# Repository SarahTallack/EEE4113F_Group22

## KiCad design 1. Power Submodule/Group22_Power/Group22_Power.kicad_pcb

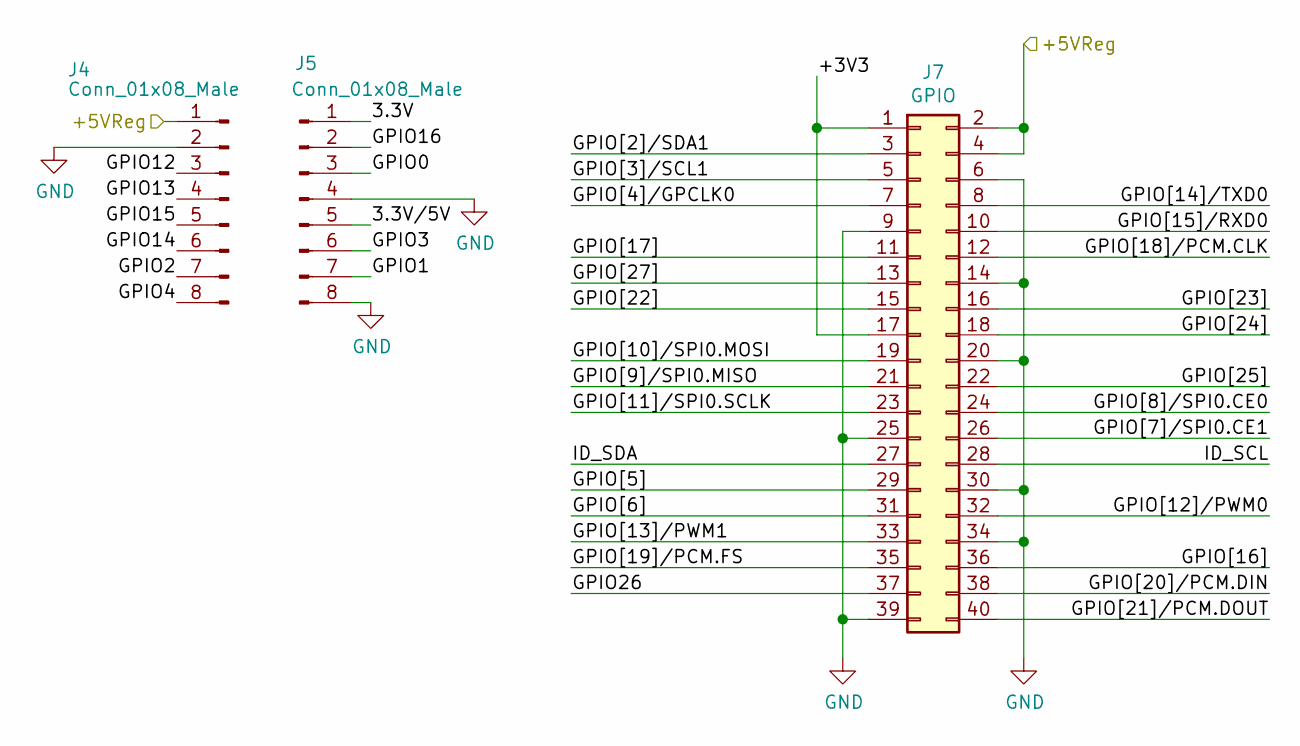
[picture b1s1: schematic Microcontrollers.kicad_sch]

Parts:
J4, J5: Conn_01x08_Male; PinSocket_1x08_P2.54mm_Vertical
J7: GPIO; PinSocket_2x20_P2.54mm_Vertical

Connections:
/Microcontrollers/3.3V: J5.1
/Microcontrollers/3.3V/5V: J5.5
/Microcontrollers/+3V3: J7.1, J7.17
/Microcontrollers/+5VReg: J4.1, J7.2, J7.4; also elsewhere on the board
/Microcontrollers/GPIO0: J5.3
/Microcontrollers/GPIO1: J5.7
/Microcontrollers/GPIO2: J4.7
/Microcontrollers/GPIO3: J5.6
/Microcontrollers/GPIO4: J4.8
/Microcontrollers/GPIO12: J4.3
/Microcontrollers/GPIO13: J4.4
/Microcontrollers/GPIO14: J4.6
/Microcontrollers/GPIO15: J4.5
/Microcontrollers/GPIO16: J5.2
/Microcontrollers/GPIO26: J7.37
/Microcontrollers/GPIO[2]/SDA1: J7.3
/Microcontrollers/GPIO[3]/SCL1: J7.5
/Microcontrollers/GPIO[4]/GPCLK0: J7.7
/Microcontrollers/GPIO[5]: J7.29
/Microcontrollers/GPIO[6]: J7.31
/Microcontrollers/GPIO[7]/SPI0.CE1: J7.26
/Microcontrollers/GPIO[8]/SPI0.CE0: J7.24
/Microcontrollers/GPIO[9]/SPI0.MISO: J7.21
/Microcontrollers/GPIO[10]/SPI0.MOSI: J7.19
/Microcontrollers/GPIO[11]/SPI0.SCLK: J7.23
/Microcontrollers/GPIO[12]/PWM0: J7.32
/Microcontrollers/GPIO[13]/PWM1: J7.33
/Microcontrollers/GPIO[14]/TXD0: J7.8
/Microcontrollers/GPIO[15]/RXD0: J7.10
/Microcontrollers/GPIO[16]: J7.36
/Microcontrollers/GPIO[17]: J7.11
/Microcontrollers/GPIO[18]/PCM.CLK: J7.12
/Microcontrollers/GPIO[19]/PCM.FS: J7.35
/Microcontrollers/GPIO[20]/PCM.DIN: J7.38
/Microcontrollers/GPIO[21]/PCM.DOUT: J7.40
/Microcontrollers/GPIO[22]: J7.15
/Microcontrollers/GPIO[23]: J7.16
/Microcontrollers/GPIO[24]: J7.18
/Microcontrollers/GPIO[25]: J7.22
/Microcontrollers/GPIO[27]: J7.13
/Microcontrollers/ID_SCL: J7.28
/Microcontrollers/ID_SDA: J7.27
GND: J4.2, J5.4, J5.8, J7.6, J7.9, J7.14, J7.20, J7.25, J7.30, J7.34, J7.39; also elsewhere on the board

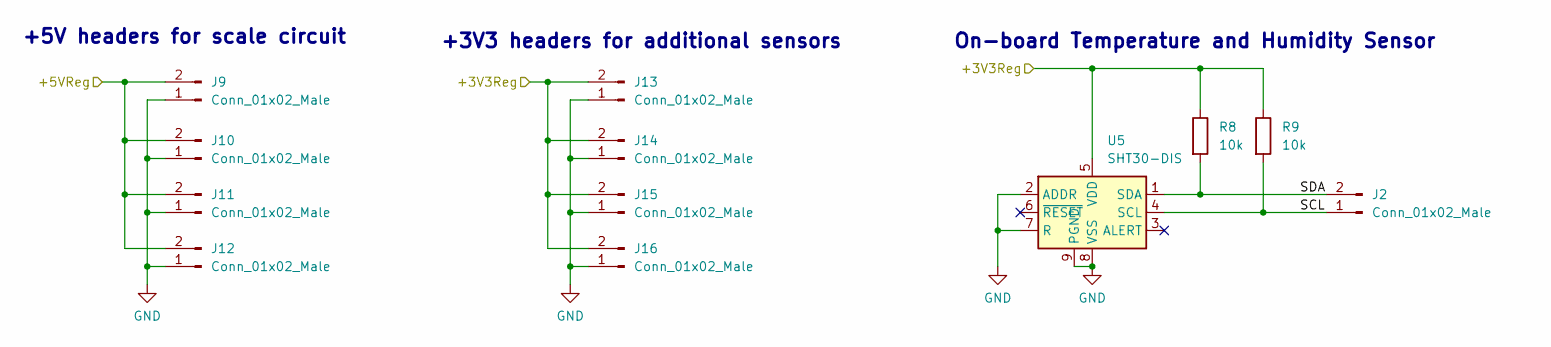
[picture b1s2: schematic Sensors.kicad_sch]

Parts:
J2, J9, J10, J11, J12, J13, J14, J15, J16: Conn_01x02_Male; PinHeader_1x02_P2.54mm_Vertical
R8, R9: 10k; R_0402_1005Metric; LCSC C25744
U5: SHT30-DIS; Sensirion_DFN-8-1EP_2.5x2.5mm_P0.5mm_EP1.1x1.7mm; LCSC C2687423

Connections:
/Microcontrollers/+5VReg: J9.2, J10.2, J11.2, J12.2; also elsewhere on the board
/Sensors/+3V3Reg: J13.2, J14.2, J15.2, J16.2, R8.1, R9.1, U5.5 (VDD); also elsewhere on the board
/Sensors/SCL: J2.1, R9.2, U5.4 (SCL)
/Sensors/SDA: J2.2, R8.2, U5.1 (SDA)
GND: J9.1, J10.1, J11.1, J12.1, J13.1, J14.1, J15.1, J16.1, U5.2 (ADDR), U5.7 (R), U5.8 (VSS), U5.9 (PGND); also elsewhere on the board

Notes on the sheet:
On-board Temperature and Humidity Sensor
+3V3 headers for additional sensors
+5V headers for scale circuit

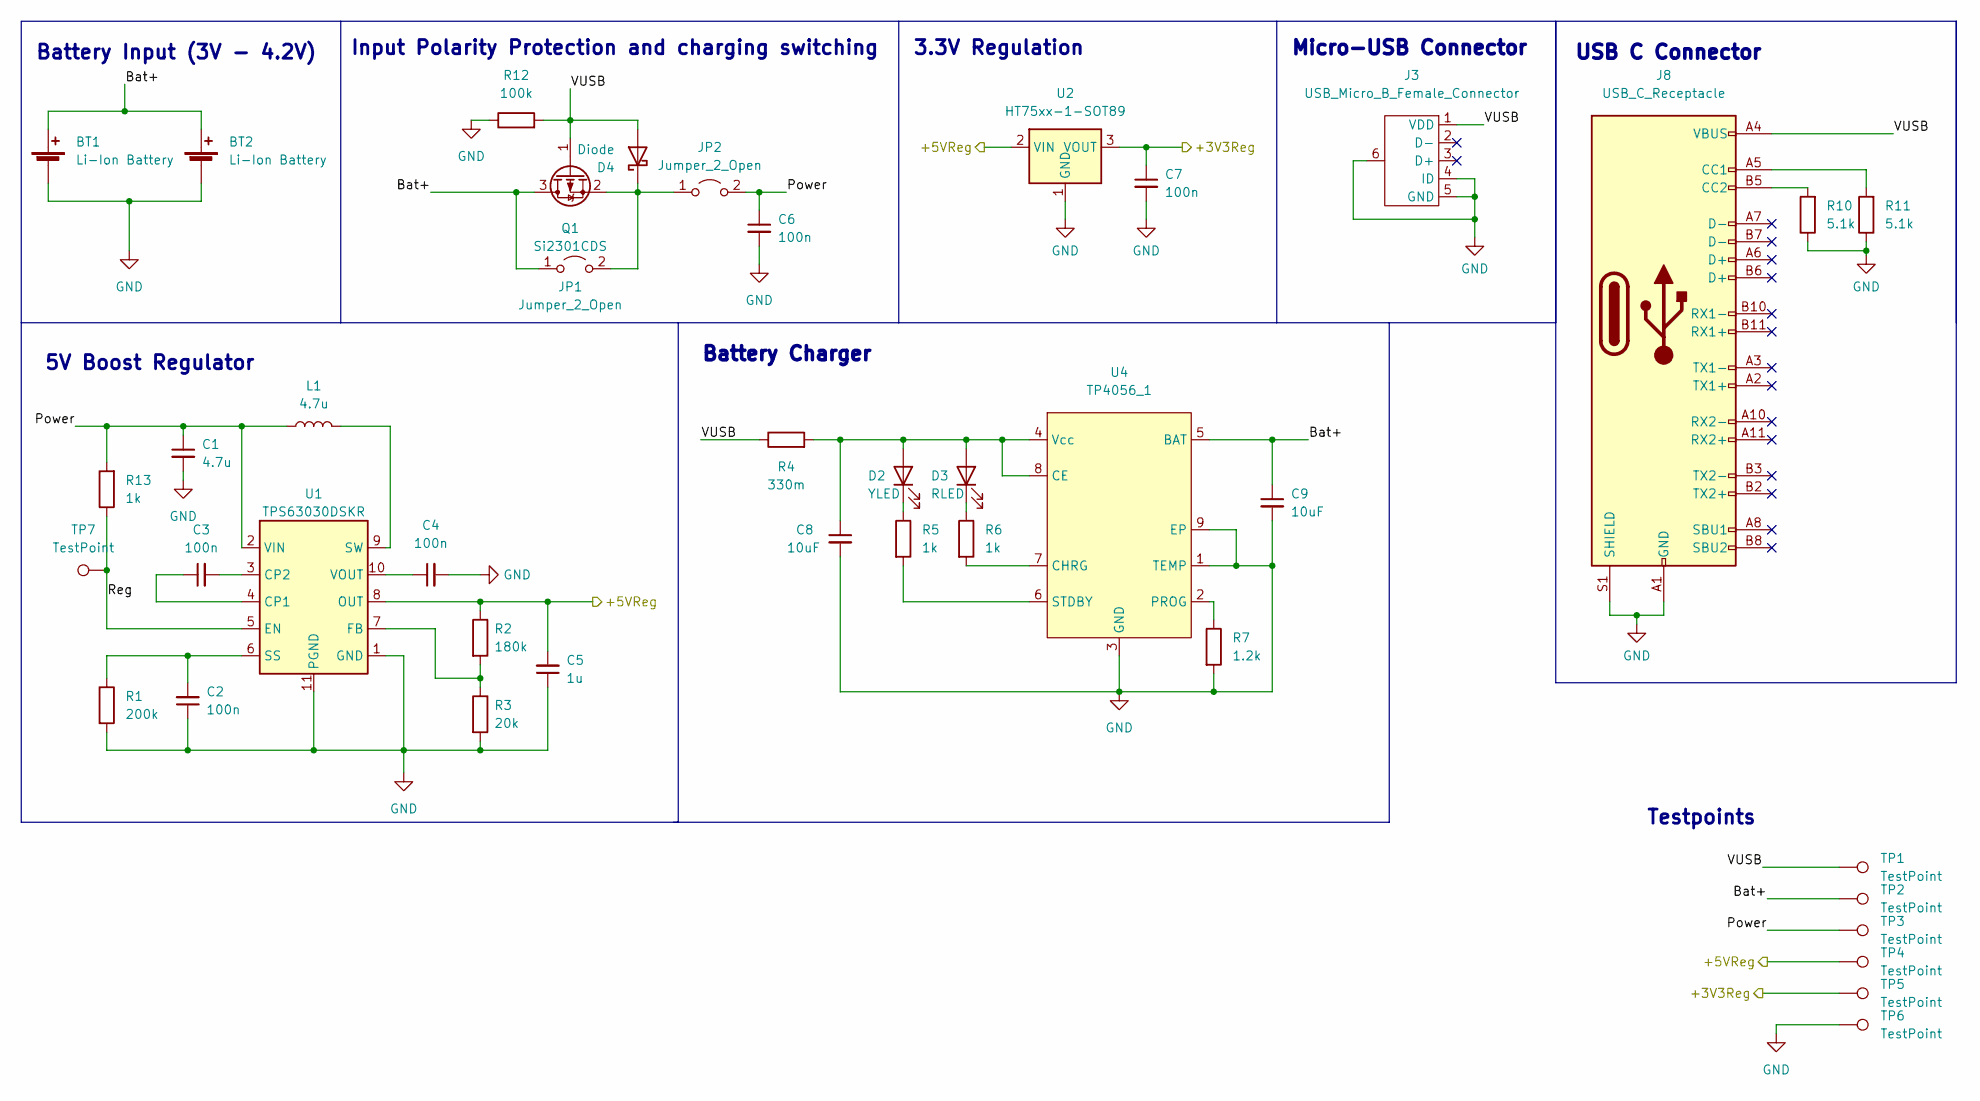
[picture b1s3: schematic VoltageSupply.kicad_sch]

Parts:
BT1, BT2: Li-Ion Battery; BatteryHolder_Keystone_1042_1x18650
C1: 4.7u; C_0805_2012Metric; LCSC C1779
C2, C3, C4, C6, C7: 100n; C_0603_1608Metric; LCSC C49678
C5: 1u; C_0805_2012Metric; LCSC C28323
C8, C9: 10uF; C_0402_1005Metric; LCSC C15525
D2: YLED; LED_0805_2012Metric; LCSC C2296
D3: RLED; LED_0603_1608Metric; LCSC C2286
D4: Diode; D_SOD-123; LCSC C8598
J3: USB_Micro_B_Female_Connector; C404969_Micro_USB; LCSC C404969
J8: USB_C_Receptacle; USB-TYPE-C-TH_USB-306A-B-SU; LCSC C309339
JP1, JP2: Jumper_2_Open; SolderJumper-2_P1.3mm_Open_RoundedPad1.0x1.5mm
L1: 4.7u; IND-SMD_L4.0-W4.0; LCSC C206275
Q1: Si2301CDS; SOT-23; LCSC C10487
R1: 200k; R_0805_2012Metric; LCSC C17539
R2: 180k; R_0603_1608Metric; LCSC C22827
R3: 20k; R_0603_1608Metric; LCSC C4184
R4: 330m; R_0805_2012Metric; LCSC C52548
R5, R6, R13: 1k; R_0603_1608Metric; LCSC C21190
R7: 1.2k; R_0603_1608Metric; LCSC C22765
R10, R11: 5.1k; R_0805_2012Metric; LCSC C27834
R12: 100k; R_0402_1005Metric; LCSC No. C25741
TP1, TP2, TP3, TP4, TP5, TP6, TP7: TestPoint; TestPoint_Pad_D2.0mm
U1: TPS63030DSKR; WSON-10-1EP_2.5x2.5mm_P0.5mm_EP1.2x2mm; LCSC C60707
U2: HT75xx-1-SOT89; SOT-89-3; LCSC C14289
U4: TP4056_1; HSOP-8-1EP_3.9x4.9mm_P1.27mm_EP2.3x2.3mm; LCSC C16581

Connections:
/Microcontrollers/+5VReg: C5.2, R2.1, TP4.1, U1.8 (OUT), U2.2 (VIN); also elsewhere on the board
/Sensors/+3V3Reg: C7.1, TP5.1, U2.3 (VOUT); also elsewhere on the board
/VoltageSupply/Bat+: BT1.1 (+), BT2.1 (+), C9.1, JP1.1 (A), Q1.3 (D), TP2.1, U4.5 (BAT)
/VoltageSupply/Power: C1.1, C6.1, JP2.2 (B), L1.1, R13.2, TP3.1, U1.2 (VIN)
/VoltageSupply/Reg: R13.1, TP7.1, U1.5 (EN)
/VoltageSupply/VUSB: D4.2 (A), J3.1 (VDD), J8.A4 (VBUS), J8.A9 (VBUS), J8.B4 (VBUS), J8.B9 (VBUS), Q1.1 (G), R4.1, R12.2, TP1.1
GND: BT1.2 (-), BT2.2 (-), C1.2, C2.1, C4.2, C5.1, C6.2, C7.2, C8.2, C9.2, J3.4 (ID), J3.5 (GND), J3.6, J8.A1 (GND), J8.A12 (GND), J8.B1 (GND), J8.B12 (GND), J8.S1 (SHIELD), R1.2, R3.2, R7.2, R10.1, R11.1, R12.1, TP6.1, U1.1 (GND), U1.11 (PGND), U2.1 (GND), U4.1 (TEMP), U4.3 (GND), U4.9 (EP); also elsewhere on the board
unnamed: C2.2, R1.1, U1.6 (SS)
unnamed: C3.1, U1.4 (CP1)
unnamed: C3.2, U1.3 (CP2)
unnamed: C4.1, U1.10 (VOUT)
unnamed: C8.1, D2.2 (A), D3.2 (A), R4.2, U4.4 (Vcc), U4.8 (CE)
unnamed: D2.1 (K), R5.1
unnamed: D3.1 (K), R6.1
unnamed: D4.1 (K), JP1.2 (B), JP2.1 (A), Q1.2 (S)
unnamed: J8.A5 (CC1), R11.2
unnamed: J8.B5 (CC2), R10.2
unnamed: L1.2, U1.9 (SW)
unnamed: R2.2, R3.1, U1.7 (FB)
unnamed: R5.2, U4.6 (STDBY)
unnamed: R6.2, U4.7 (CHRG)
unnamed: R7.1, U4.2 (PROG)

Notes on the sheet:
3.3V Regulation
Battery Input (3V - 4.2V)
Micro-USB Connector
5V Boost Regulator
Testpoints
Battery Charger
Input Polarity Protection and charging switching
USB C Connector

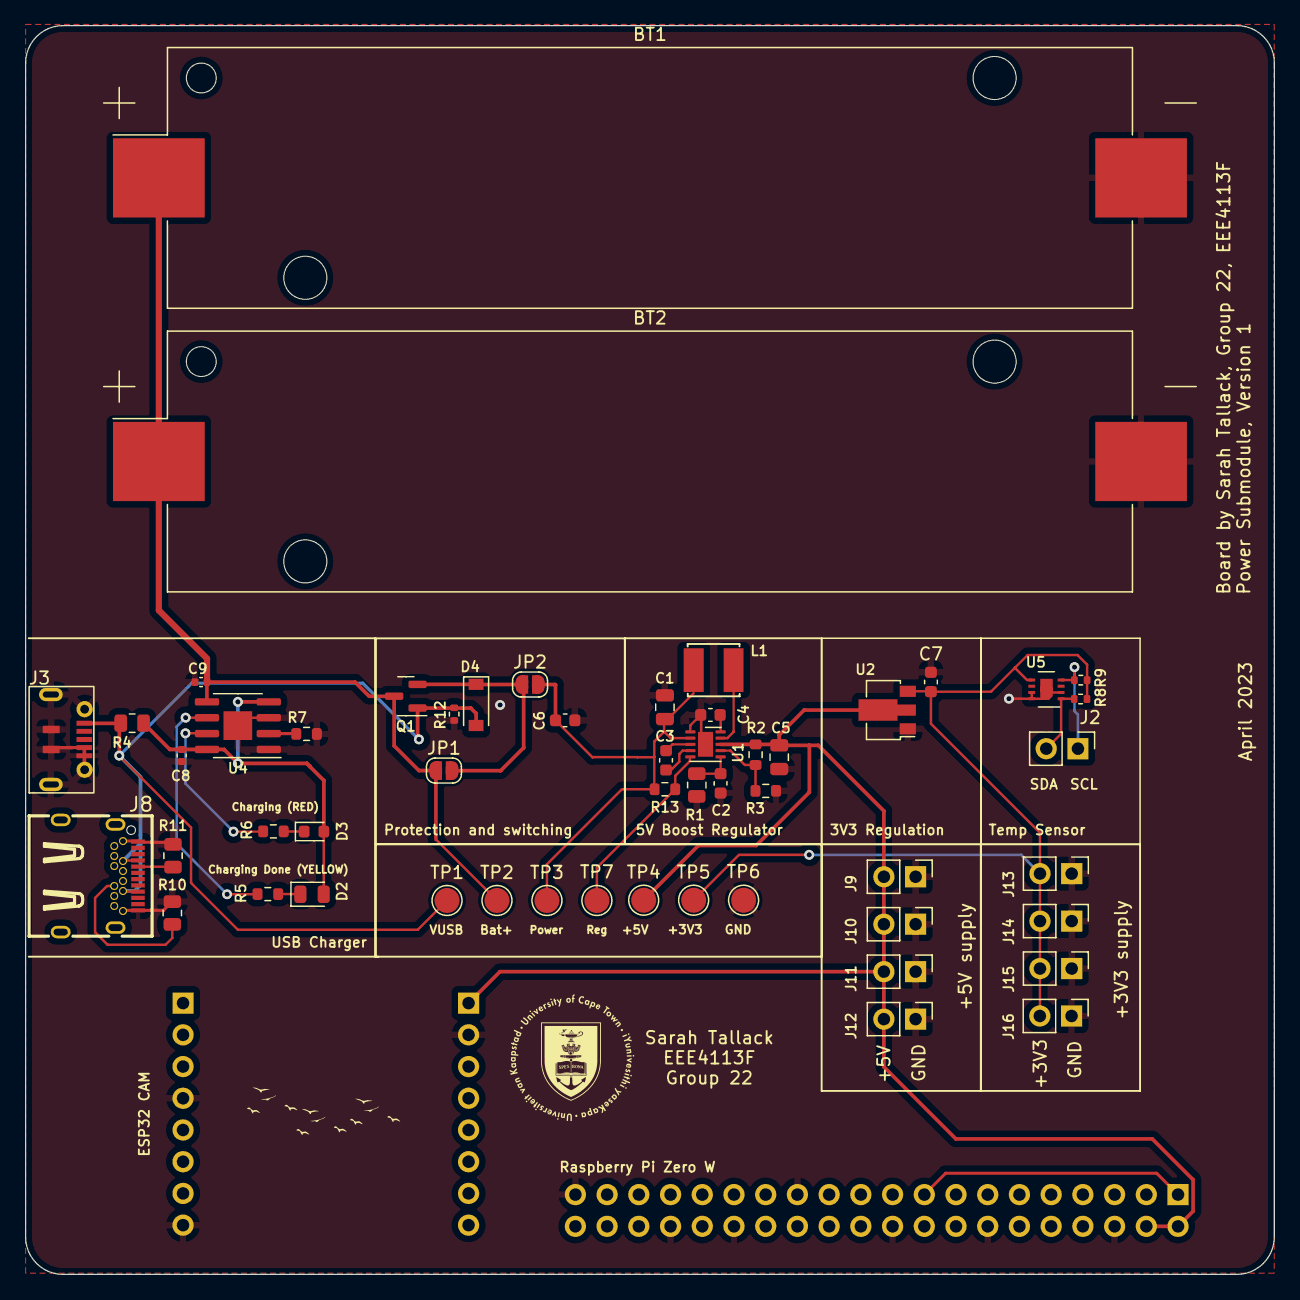
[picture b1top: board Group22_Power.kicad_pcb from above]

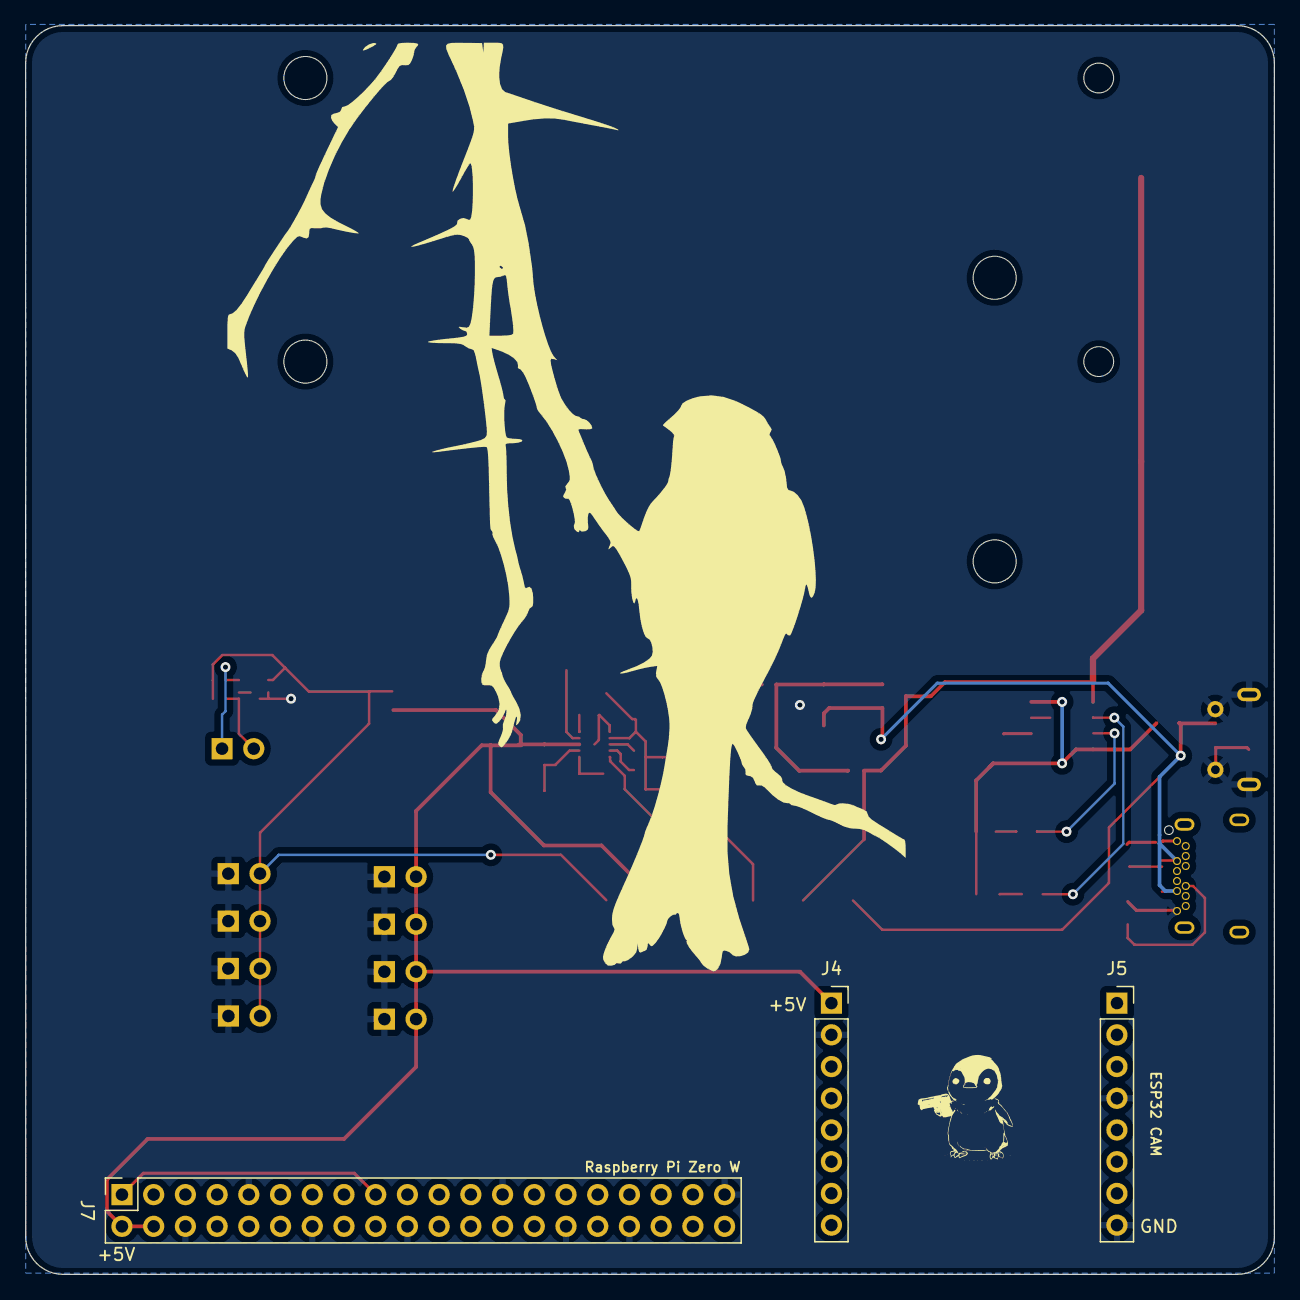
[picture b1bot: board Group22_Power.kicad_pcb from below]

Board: 2 copper layers, 100.0 x 100.0 mm, 56 parts (3 on the bottom side), 25 nets.

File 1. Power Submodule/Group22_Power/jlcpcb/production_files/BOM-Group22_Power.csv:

Comment,Designator,Footprint,LCSC
Si2301CDS,Q1,SOT-23,C10487
HT75xx-1-SOT89,U2,SOT-89-3,C14289
10uF,"C8,C9",C_0402_1005Metric,C15525
TP4056_1,U4,HSOP-8-1EP_3.9x4.9mm_P1.27mm_EP2.3x2.3mm,C16581
200k,R1,R_0805_2012Metric,C17539
4.7u,C1,C_0805_2012Metric,C1779
4.7u,L1,IND-SMD_L4.0-W4.0,C206275
1k,"R13,R5,R6",R_0603_1608Metric,C21190
1.2k,R7,R_0603_1608Metric,C22765
180k,R2,R_0603_1608Metric,C22827
RLED,D3,LED_0603_1608Metric,C2286
YLED,D2,LED_0805_2012Metric,C2296
100k,R12,R_0402_1005Metric,C25741
10k,"R8,R9",R_0402_1005Metric,C25744
5.1k,"R10,R11",R_0805_2012Metric,C27834
1u,C5,C_0805_2012Metric,C28323
USB_C_Receptacle,J8,USB-TYPE-C-TH_USB-306A-B-SU,C309339
USB_Micro_B_Female_Connector,J3,C404969_Micro_USB,C404969
20k,R3,R_0603_1608Metric,C4184
Conn_01x02_Male,J2,PinHeader_1x02_P2.54mm_Vertical,C492401
100n,"C2,C3,C4,C6,C7",C_0603_1608Metric,C49678
330m,R4,R_0805_2012Metric,C52548
TPS63030DSKR,U1,WSON-10-1EP_2.5x2.5mm_P0.5mm_EP1.2x2mm,C60707
SHT30-DIS,U5,Sensirion_DFN-8-1EP_2.5x2.5mm_P0.5mm_EP1.1x1.7mm,C77361
Diode,D4,D_SOD-123,C8598
TestPoint,TP5,TestPoint_Pad_D2.0mm,
TestPoint,TP4,TestPoint_Pad_D2.0mm,
TestPoint,TP3,TestPoint_Pad_D2.0mm,
TestPoint,TP2,TestPoint_Pad_D2.0mm,
TestPoint,TP1,TestPoint_Pad_D2.0mm,
Li-Ion Battery,BT2,BatteryHolder_Keystone_1042_1x18650,
Li-Ion Battery,BT1,BatteryHolder_Keystone_1042_1x18650,
TestPoint,TP7,TestPoint_Pad_D2.0mm,
Conn_01x02_Male,J12,PinHeader_1x02_P2.54mm_Vertical,
TestPoint,TP6,TestPoint_Pad_D2.0mm,
Conn_01x02_Male,J15,PinHeader_1x02_P2.54mm_Vertical,
Conn_01x02_Male,J14,PinHeader_1x02_P2.54mm_Vertical,
Conn_01x02_Male,J16,PinHeader_1x02_P2.54mm_Vertical,
Conn_01x02_Male,J11,PinHeader_1x02_P2.54mm_Vertical,
Conn_01x02_Male,J13,PinHeader_1x02_P2.54mm_Vertical,
Conn_01x02_Male,J9,PinHeader_1x02_P2.54mm_Vertical,
Conn_01x02_Male,J10,PinHeader_1x02_P2.54mm_Vertical,
Conn_01x08_Male,J4,PinSocket_1x08_P2.54mm_Vertical,
GPIO,J7,PinSocket_2x20_P2.54mm_Vertical,
Conn_01x08_Male,J5,PinSocket_1x08_P2.54mm_Vertical,
Jumper_2_Open,JP2,SolderJumper-2_P1.3mm_Open_RoundedPad1.0x1.5mm,
Jumper_2_Open,JP1,SolderJumper-2_P1.3mm_Open_RoundedPad1.0x1.5mm,

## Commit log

2023-04-16 power pcb
2023-04-17 power
2023-04-19 pcb done
2023-05-07 power:
2023-05-21 Power Submodule
